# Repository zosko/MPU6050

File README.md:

# MPU6050-module
MPU6050 Module board

## Scheme

## Board

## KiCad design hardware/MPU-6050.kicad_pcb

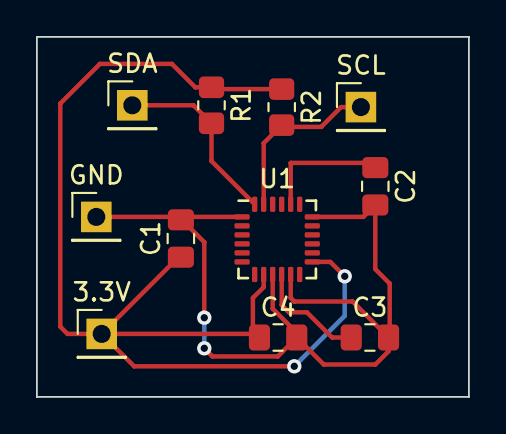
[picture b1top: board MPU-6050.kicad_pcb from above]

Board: 2 copper layers, 24.0 x 20.0 mm, 11 parts (0 on the bottom side), 6 nets.

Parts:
3.3V: 3.3V; PinHeader_1x01_P2.54mm_Vertical
C1, C3: 100nF; C_0805_2012Metric_Pad1.18x1.45mm_HandSolder
C2: 2.2nF; C_0805_2012Metric_Pad1.18x1.45mm_HandSolder
C4: 10nF; C_0805_2012Metric_Pad1.18x1.45mm_HandSolder
GND: GND; PinHeader_1x01_P2.54mm_Vertical
R1, R2: 4.7K; R_0805_2012Metric_Pad1.20x1.40mm_HandSolder
SCL: SCL; PinHeader_1x01_P2.54mm_Vertical
SDA: SDA; PinHeader_1x01_P2.54mm_Vertical
U1: MPU-6050; InvenSense_QFN-24_4x4mm_P0.5mm

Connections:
3.3V: 3.3V.1, C1.1, C4.1, R1.1, R2.1, U1.8 (VLOGIC), U1.13 (VDD)
GND: C1.2, C2.2, C3.2, C4.2, GND.1, U1.1 (CLKIN), U1.9 (AD0), U1.11 (FSYNC), U1.18 (GND)
unnamed: C2.1, U1.20 (CPOUT)
unnamed: C3.1, U1.10 (REGOUT)
SCL: R2.2, SCL.1, U1.23 (SCL)
SDA: R1.2, SDA.1, U1.24 (SDA)
